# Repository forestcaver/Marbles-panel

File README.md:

# Marbles-Panel

1. My version of the marbles panel - bitmap, eagle files, gerbers
2. My spreadsheet to calibrate marbles and my version of settings.cc which includes my calibration data for my two modules.
3. Calibration document written by Bu Ma from some rough notes I sent - his are very clear instructions ! (Reproduced here by kind permission of Bu Ma !)
4. NOTE: When flashing the module make sure to erase flash first.
5. Added a mic803 supervisor, moved recom to the back of the pcb so it doesnt clash with the switch

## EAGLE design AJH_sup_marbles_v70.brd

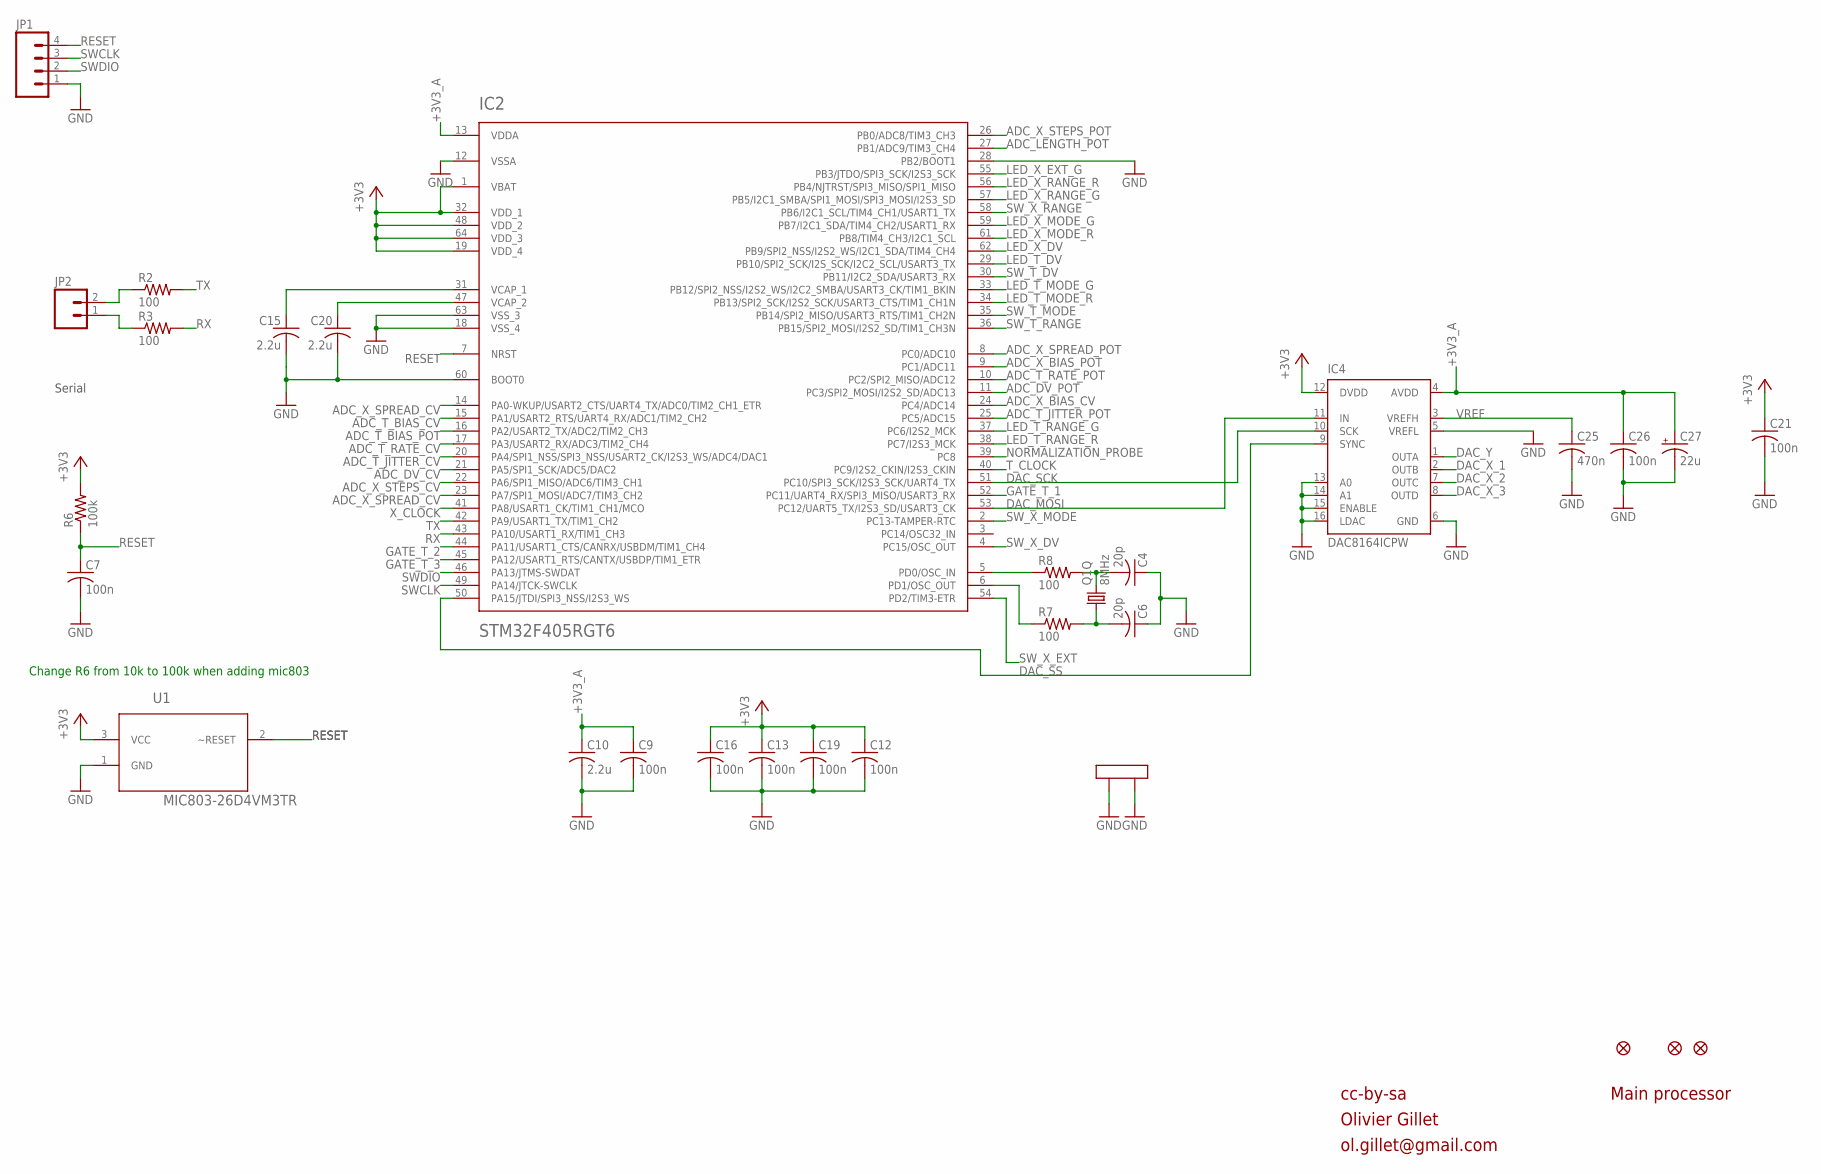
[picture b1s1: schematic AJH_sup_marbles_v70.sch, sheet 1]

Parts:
C4, C6: 20p; C0402
C7, C9, C12, C13, C16, C19, C21, C26: 100n; C0402
C10, C15, C20: 2.2u; C0805
C25: 470n; C0402
C27: 22u; PANASONIC_C
F1, F2, F3: FIDUCIAL1X2; FIDUCIAL-1X2
IC2: STM32F405RGT6; TQFP-10X10-64
IC4: DAC8164ICPW; SOP65P640X110-16N
JP1: M04PTH; 1X04
JP2: M02PTH; 1X02
Q1: 8MHz; CTS406
R2, R3, R7, R8: 100; R0402
R6: 100k; R0402
U1: MIC803-26D4VM3TR; SOT95P232X110-3N

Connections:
+3V3: C12.1, C13.1, C16.1, C19.1, C21.1, IC2.1 (VBAT), IC2.19 (VDD_4), IC2.32 (VDD_1), IC2.48 (VDD_2), IC2.64 (VDD_3), IC4.12 (DVDD), R6.2, U1.3 (VCC); also elsewhere on the board
+3V3_A: C9.1, C10.1, C26.1, C27.+, IC2.13 (VDDA), IC4.4 (AVDD); also elsewhere on the board
ADC_DV_CV: IC2.21 (PA5/SPI1_SCK/ADC5/DAC2); also elsewhere on the board
ADC_DV_POT: IC2.11 (PC3/SPI2_MOSI/I2S2_SD/ADC13); also elsewhere on the board
ADC_LENGTH_POT: IC2.27 (PB1/ADC9/TIM3_CH4); also elsewhere on the board
ADC_T_BIAS_CV: IC2.15 (PA1/USART2_RTS/UART4_RX/ADC1/TIM2_CH2); also elsewhere on the board
ADC_T_BIAS_POT: IC2.16 (PA2/USART2_TX/ADC2/TIM2_CH3); also elsewhere on the board
ADC_T_JITTER_CV: IC2.20 (PA4/SPI1_NSS/SPI3_NSS/USART2_CK/I2S3_WS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); also elsewhere on the board
ADC_T_JITTER_POT: IC2.25 (PC5/ADC15); also elsewhere on the board
ADC_T_RATE_CV: IC2.17 (PA3/USART2_RX/ADC3/TIM2_CH4); also elsewhere on the board
ADC_T_RATE_POT: IC2.10 (PC2/SPI2_MISO/ADC12); also elsewhere on the board
ADC_X_BIAS_CV: IC2.24 (PC4/ADC14); also elsewhere on the board
ADC_X_BIAS_POT: IC2.9 (PC1/ADC11); also elsewhere on the board
ADC_X_SPREAD_CV: IC2.14 (PA0-WKUP/USART2_CTS/UART4_TX/ADC0/TIM2_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), IC2.23 (PA7/SPI1_MOSI/ADC7/TIM3_CH2); also elsewhere on the board
ADC_X_SPREAD_POT: IC2.8 (PC0/ADC10); also elsewhere on the board
ADC_X_STEPS_CV: IC2.22 (PA6/SPI1_MISO/ADC6/TIM3_CH1); also elsewhere on the board
ADC_X_STEPS_POT: IC2.26 (PB0/ADC8/TIM3_CH3); also elsewhere on the board
DAC_MOSI: IC2.53 (PC12/UART5_TX/I2S3_SD/USART3_CK), IC4.11 (IN)
DAC_SCK: IC2.51 (PC10/SPI3_SCK/I2S3_SCK/UART4_TX), IC4.10 (SCK)
DAC_SS: IC2.50 (PA15/JTDI/SPI3_NSS/I2S3_WS), IC4.9 (SYNC)
DAC_X_1: IC4.2 (OUTB); also elsewhere on the board
DAC_X_2: IC4.7 (OUTC); also elsewhere on the board
DAC_X_3: IC4.8 (OUTD); also elsewhere on the board
DAC_Y: IC4.1 (OUTA); also elsewhere on the board
GATE_T_1: IC2.52 (PC11/UART4_RX/SPI3_MISO/USART3_RX); also elsewhere on the board
GATE_T_2: IC2.44 (PA11/USART1_CTS/CANRX/USBDM/TIM1_CH4); also elsewhere on the board
GATE_T_3: IC2.45 (PA12/USART1_RTS/CANTX/USBDP/TIM1_ETR); also elsewhere on the board
GND: C4.1, C6.1, C7.2, C9.2, C10.2, C12.2, C13.2, C15.2, C16.2, C19.2, C20.2, C21.2, C25.2, C26.2, C27.-, IC2.12 (VSSA), IC2.18 (VSS_4), IC2.28 (PB2/BOOT1), IC2.60 (BOOT0), IC2.63 (VSS_3), IC4.5 (VREFL), IC4.6 (GND), IC4.13 (A0), IC4.14 (A1), IC4.15 (ENABLE), IC4.16 (LDAC), JP1.1, Q1.2 (LID1), Q1.4 (LID2), U1.1 (GND); also elsewhere on the board
LED_T_DV: IC2.29 (PB10/SPI2_SCK/I2S_SCK/I2C2_SCL/USART3_TX); also elsewhere on the board
LED_T_MODE_G: IC2.33 (PB12/SPI2_NSS/I2S2_WS/I2C2_SMBA/USART3_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); also elsewhere on the board
LED_T_MODE_R: IC2.34 (PB13/SPI2_SCK/I2S2_SCK/USART3_CTS/TIM1_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); also elsewhere on the board
LED_T_RANGE_G: IC2.37 (PC6/I2S2_MCK); also elsewhere on the board
LED_T_RANGE_R: IC2.38 (PC7/I2S3_MCK); also elsewhere on the board
LED_X_DV: IC2.62 (PB9/SPI2_NSS/I2S2_WS/I2C1_SDA/TIM4_CH4); also elsewhere on the board
LED_X_EXT_G: IC2.55 (PB3/JTDO/SPI3_SCK/I2S3_SCK); also elsewhere on the board
LED_X_MODE_G: IC2.59 (PB7/I2C1_SDA/TIM4_CH2/USART1_RX); also elsewhere on the board
LED_X_MODE_R: IC2.61 (PB8/TIM4_CH3/I2C1_SCL); also elsewhere on the board
LED_X_RANGE_G: IC2.57 (PB5/I2C1_SMBA/SPI1_MOSI/SPI3_MOSI/I2S3_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); also elsewhere on the board
LED_X_RANGE_R: IC2.56 (PB4/NJTRST/SPI3_MISO/SPI1_MISO); also elsewhere on the board
unnamed: IC2.6 (PD1/OSC_OUT), R7.1
unnamed: IC2.5 (PD0/OSC_IN), R8.1
unnamed: C20.1, IC2.47 (VCAP_2)
unnamed: C15.1, IC2.31 (VCAP_1)
unnamed: JP2.2, R2.1
unnamed: JP2.1, R3.1
unnamed: C4.2, Q1.3 (2), R8.2
unnamed: C6.2, Q1.1, R7.2
NORMALIZATION_PROBE: IC2.39 (PC8); also elsewhere on the board
RESET: C7.1, IC2.7 (NRST), JP1.4, R6.1, U1.2 (~RESET)
RX: IC2.43 (PA10/USART1_RX/TIM1_CH3), R3.2
SWCLK: IC2.49 (PA14/JTCK-SWCLK), JP1.3
SWDIO: IC2.46 (PA13/JTMS-SWDAT), JP1.2
SW_T_DV: IC2.30 (PB11/I2C2_SDA/USART3_RX); also elsewhere on the board
SW_T_MODE: IC2.35 (PB14/SPI2_MISO/USART3_RTS/TIM1_CH2N); also elsewhere on the board
SW_T_RANGE: IC2.36 (PB15/SPI2_MOSI/I2S2_SD/TIM1_CH3N); also elsewhere on the board
SW_X_DV: IC2.4 (PC15/OSC_OUT); also elsewhere on the board
SW_X_EXT: IC2.54 (PD2/TIM3-ETR); also elsewhere on the board
SW_X_MODE: IC2.2 (PC13-TAMPER-RTC); also elsewhere on the board
SW_X_RANGE: IC2.58 (PB6/I2C1_SCL/TIM4_CH1/USART1_TX); also elsewhere on the board
TX: IC2.42 (PA9/USART1_TX/TIM1_CH2), R2.2
T_CLOCK: IC2.40 (PC9/I2S2_CKIN/I2S3_CKIN); also elsewhere on the board
VREF: C25.1, IC4.3 (VREFH); also elsewhere on the board
X_CLOCK: IC2.41 (PA8/USART1_CK/TIM1_CH1/MCO); also elsewhere on the board

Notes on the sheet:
cc-by-sa
Olivier Gillet
ol.gillet@gmail.com
Main processor
Serial
Change R6 from 10k to 100k when adding mic803

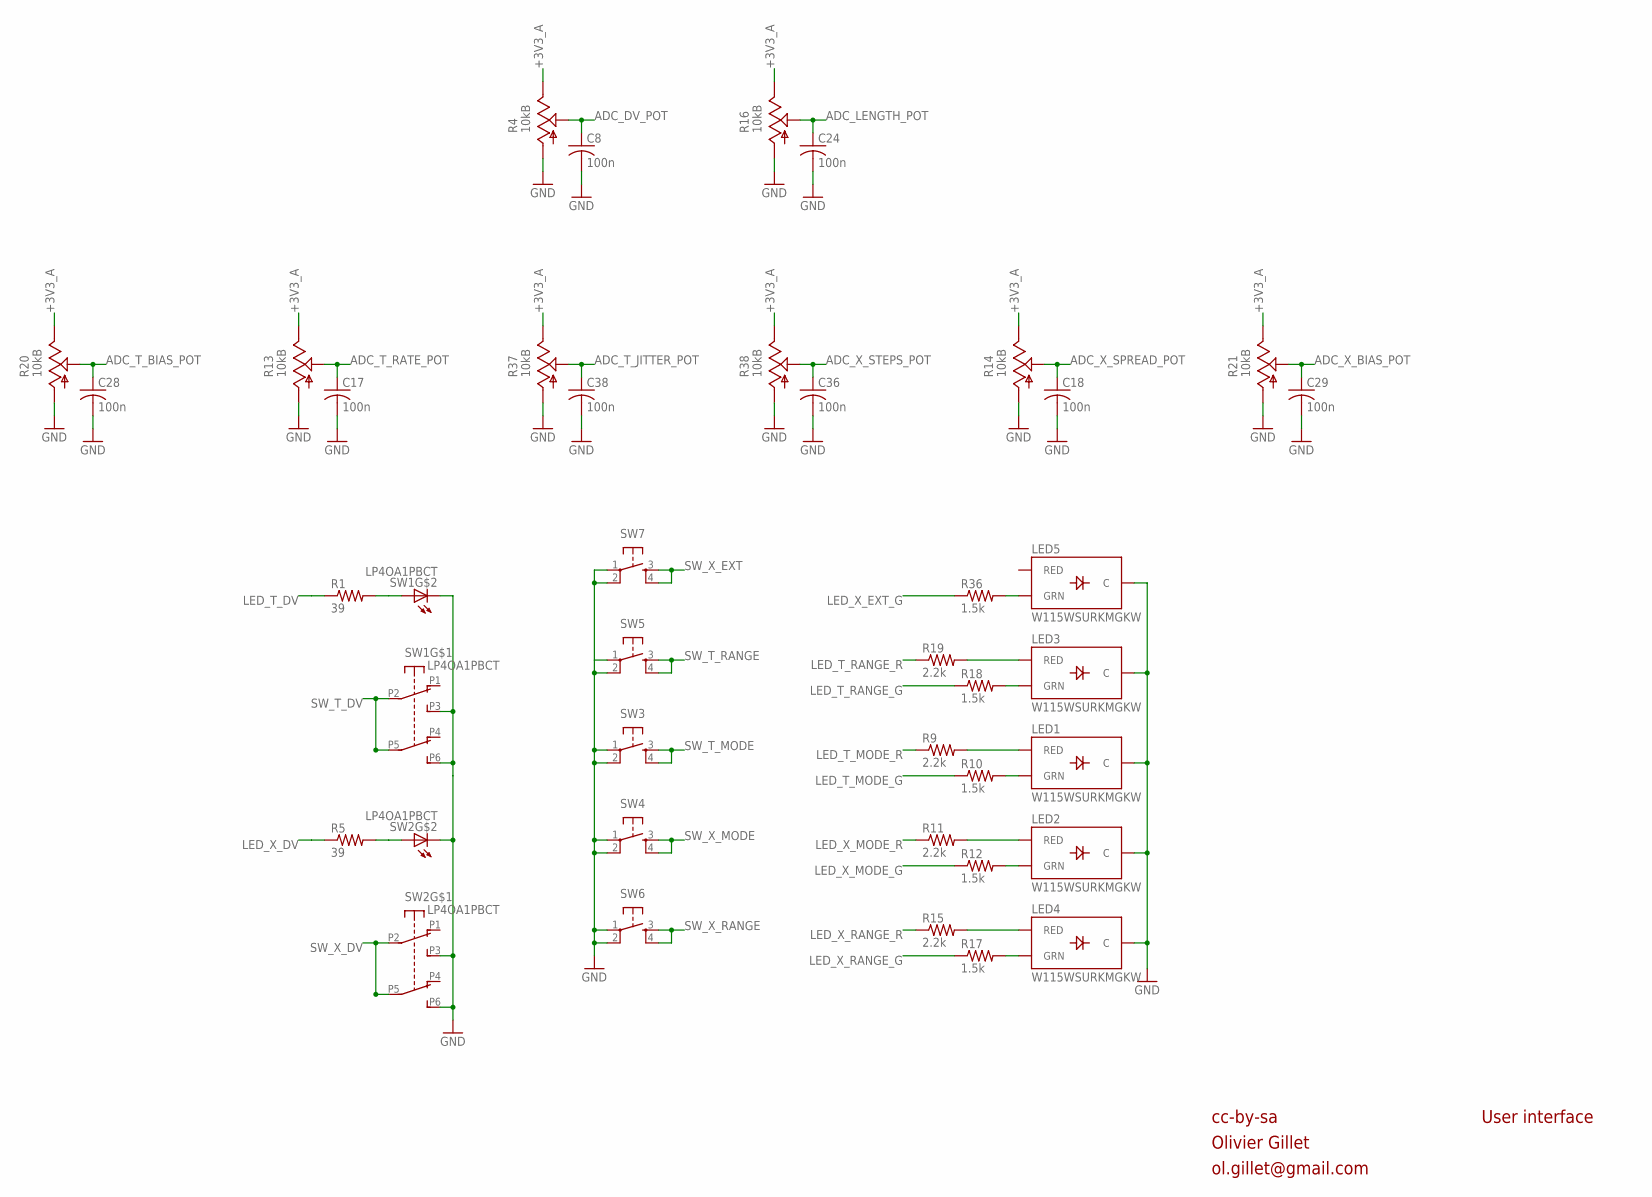
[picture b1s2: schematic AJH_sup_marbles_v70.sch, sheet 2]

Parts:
C8, C17, C18, C24, C28, C29, C36, C38: 100n; C0402
LED1, LED2, LED3, LED4, LED5: W115WSURKMGKW; LED-BICOLOR-THROUGHHOLE-2.54
R1, R5: 39; R0402
R4, R13, R14, R16, R20, R21, R37, R38: 10kB; ALPS_POT_VERTICAL_PS
R9, R11, R15, R19: 2.2k; R0402
R10, R12, R17, R18, R36: 1.5k; R0402
SW1, SW2: LP4OA1PBCT
SW3, SW4, SW5, SW6, SW7: TAC_SWITCHPTH; TACTILE-PTH

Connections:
+3V3_A: R4.P$1 (E), R13.P$1 (E), R14.P$1 (E), R16.P$1 (E), R20.P$1 (E), R21.P$1 (E), R37.P$1 (E), R38.P$1 (E); also elsewhere on the board
ADC_DV_POT: C8.1, R4.P$2 (S); also elsewhere on the board
ADC_LENGTH_POT: C24.1, R16.P$2 (S); also elsewhere on the board
ADC_T_BIAS_POT: C28.1, R20.P$2 (S); also elsewhere on the board
ADC_T_JITTER_POT: C38.1, R37.P$2 (S); also elsewhere on the board
ADC_T_RATE_POT: C17.1, R13.P$2 (S); also elsewhere on the board
ADC_X_BIAS_POT: C29.1, R21.P$2 (S); also elsewhere on the board
ADC_X_SPREAD_POT: C18.1, R14.P$2 (S); also elsewhere on the board
ADC_X_STEPS_POT: C36.1, R38.P$2 (S); also elsewhere on the board
GND: C8.2, C17.2, C18.2, C24.2, C28.2, C29.2, C36.2, C38.2, LED1.2 (C), LED2.2 (C), LED3.2 (C), LED4.2 (C), LED5.2 (C), R4.P$3 (A), R13.P$3 (A), R14.P$3 (A), R16.P$3 (A), R20.P$3 (A), R21.P$3 (A), R37.P$3 (A), R38.P$3 (A), SW1.L2, SW1.P3 (A3), SW1.P6 (B3), SW2.L2, SW2.P3 (A3), SW2.P6 (B3), SW3.1, SW3.2, SW4.1, SW4.2, SW5.1, SW5.2, SW6.1, SW6.2, SW7.1, SW7.2; also elsewhere on the board
LED_T_DV: R1.1; also elsewhere on the board
LED_T_MODE_G: R10.1; also elsewhere on the board
LED_T_MODE_R: R9.1; also elsewhere on the board
LED_T_RANGE_G: R18.1; also elsewhere on the board
LED_T_RANGE_R: R19.1; also elsewhere on the board
LED_X_DV: R5.1; also elsewhere on the board
LED_X_EXT_G: R36.1; also elsewhere on the board
LED_X_MODE_G: R12.1; also elsewhere on the board
LED_X_MODE_R: R11.1; also elsewhere on the board
LED_X_RANGE_G: R17.1; also elsewhere on the board
LED_X_RANGE_R: R15.1; also elsewhere on the board
unnamed: R1.2, SW1.L1
unnamed: R5.2, SW2.L1
unnamed: LED3.3 (RED), R19.2
unnamed: LED3.1 (GRN), R18.2
unnamed: LED1.3 (RED), R9.2
unnamed: LED2.3 (RED), R11.2
unnamed: LED2.1 (GRN), R12.2
unnamed: LED4.3 (RED), R15.2
unnamed: LED1.1 (GRN), R10.2
unnamed: LED4.1 (GRN), R17.2
unnamed: LED5.1 (GRN), R36.2
SW_T_DV: SW1.P2 (A2), SW1.P5 (B2); also elsewhere on the board
SW_T_MODE: SW3.3, SW3.4; also elsewhere on the board
SW_T_RANGE: SW5.3, SW5.4; also elsewhere on the board
SW_X_DV: SW2.P2 (A2), SW2.P5 (B2); also elsewhere on the board
SW_X_EXT: SW7.3, SW7.4; also elsewhere on the board
SW_X_MODE: SW4.3, SW4.4; also elsewhere on the board
SW_X_RANGE: SW6.3, SW6.4; also elsewhere on the board

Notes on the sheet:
cc-by-sa
Olivier Gillet
ol.gillet@gmail.com
User interface

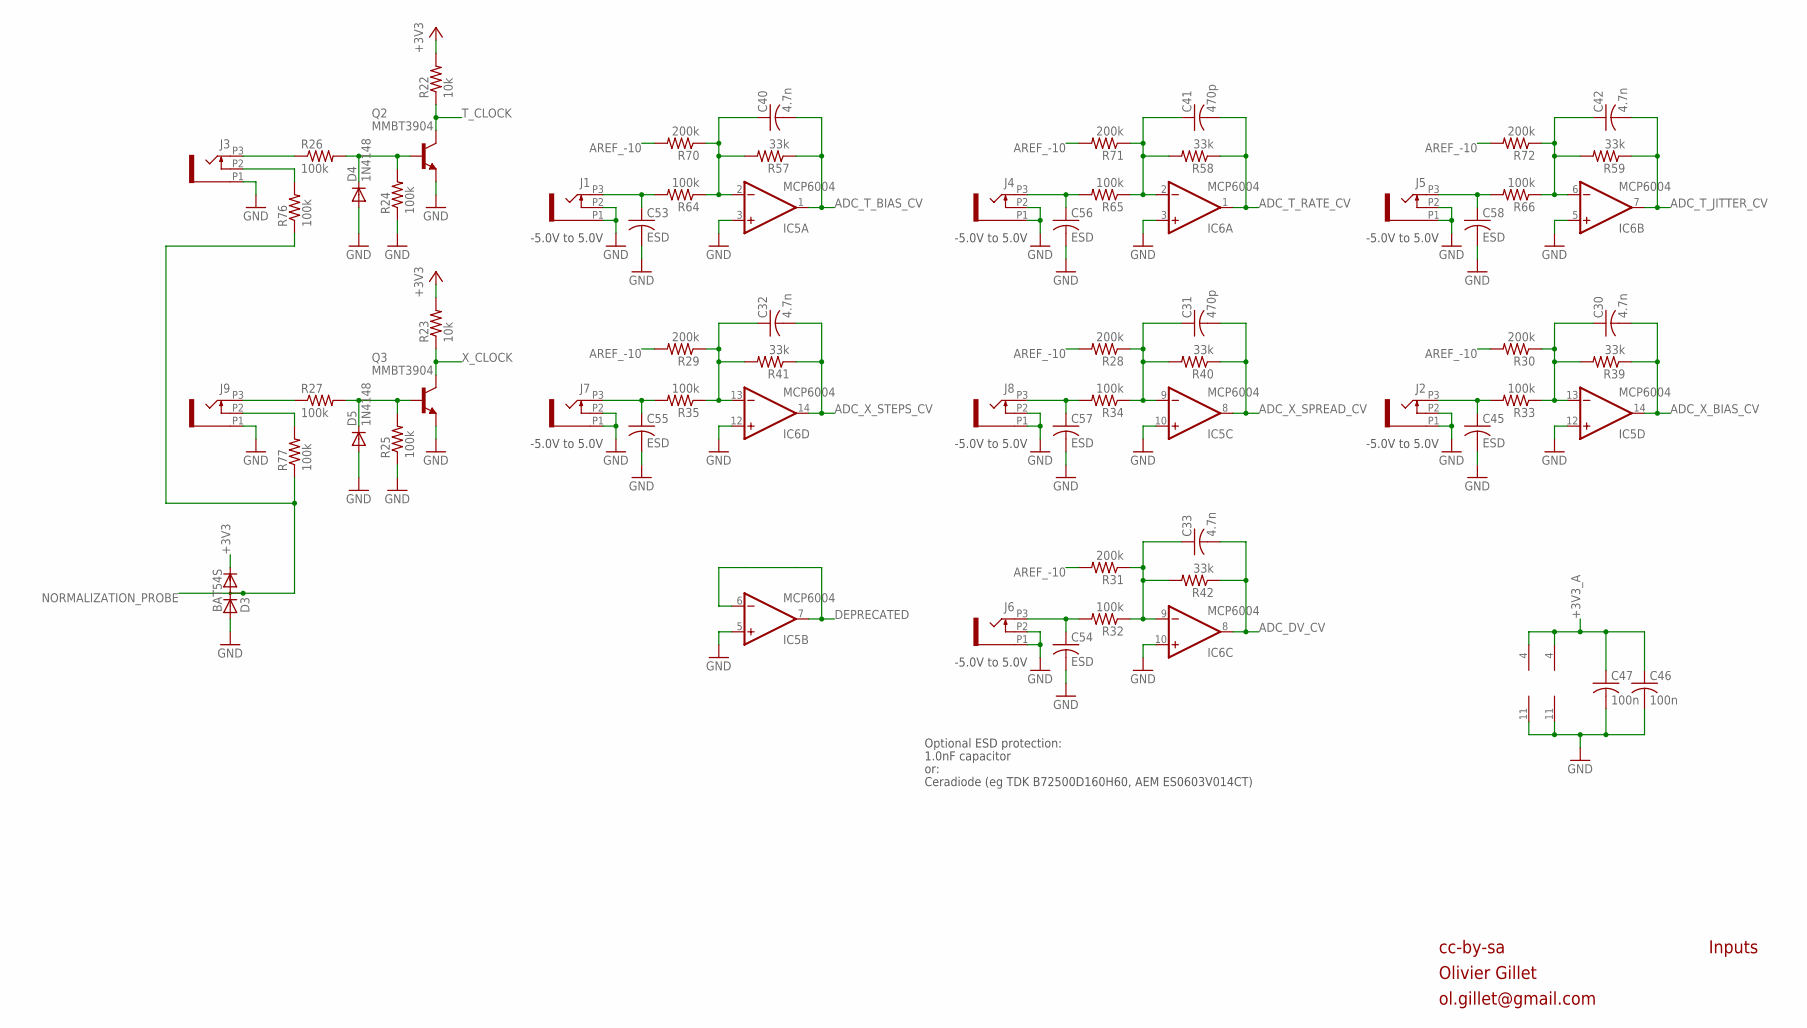
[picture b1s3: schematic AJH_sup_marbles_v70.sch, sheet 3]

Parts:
C30, C32, C33, C40, C42: 4.7n; C0402
C31, C41: 470p; C0402
C45, C53, C54, C55, C56, C57, C58: ESD; C0603
C46, C47: 100n; C0402
D3: BAT54S; SOT23
D4, D5: 1N4148; SOD523
IC5, IC6: MCP6004; TSSOP14_065
J1, J2, J3, J4, J5, J6, J7, J8, J9: PJ301_THONKICONN6; WQP_PJ_301M6
Q2, Q3: MMBT3904; SOT23-BEC
R22, R23: 10k; R0402
R24, R25, R26, R27, R32, R33, R34, R35, R64, R65, R66, R76, R77: 100k; R0402
R28, R29, R30, R31, R70, R71, R72: 200k; R0402
R39, R40, R41, R42, R57, R58, R59: 33k; R0402

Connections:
+3V3: D3.2 (C), R22.2, R23.2; also elsewhere on the board
+3V3_A: C46.1, C47.1, IC5.4 (V+), IC6.4 (V+); also elsewhere on the board
ADC_DV_CV: C33.2, IC6.8 (OUT), R42.1; also elsewhere on the board
ADC_T_BIAS_CV: C40.2, IC5.1 (OUT), R57.1; also elsewhere on the board
ADC_T_JITTER_CV: C42.2, IC6.7 (OUT), R59.1; also elsewhere on the board
ADC_T_RATE_CV: C41.2, IC6.1 (OUT), R58.1; also elsewhere on the board
ADC_X_BIAS_CV: C30.2, IC5.14 (OUT), R39.1; also elsewhere on the board
ADC_X_SPREAD_CV: C31.2, IC5.8 (OUT), R40.1; also elsewhere on the board
ADC_X_STEPS_CV: C32.2, IC6.14 (OUT), R41.1; also elsewhere on the board
AREF_-10: R28.2, R29.2, R30.2, R31.2, R70.2, R71.2, R72.2; also elsewhere on the board
DEPRECATED: IC5.6 (-IN), IC5.7 (OUT)
GND: C45.2, C46.2, C47.2, C53.2, C54.2, C55.2, C56.2, C57.2, C58.2, D3.1 (A), D4.A, D5.A, IC5.3 (+IN), IC5.5 (+IN), IC5.10 (+IN), IC5.11 (V-), IC5.12 (+IN), IC6.3 (+IN), IC6.5 (+IN), IC6.10 (+IN), IC6.11 (V-), IC6.12 (+IN), J1.P1 (1), J1.P2 (2), J2.P1 (1), J2.P2 (2), J3.P1 (1), J4.P1 (1), J4.P2 (2), J5.P1 (1), J5.P2 (2), J6.P1 (1), J6.P2 (2), J7.P1 (1), J7.P2 (2), J8.P1 (1), J8.P2 (2), J9.P1 (1), Q2.E, Q3.E, R24.1, R25.1; also elsewhere on the board
MORPH_IN: C53.1, J1.P3 (3), R64.2
MORPH_IN1: C55.1, J7.P3 (3), R35.2
MORPH_IN3: C56.1, J4.P3 (3), R65.2
MORPH_IN4: C57.1, J8.P3 (3), R34.2
MORPH_IN5: C54.1, J6.P3 (3), R32.2
MORPH_IN6: C58.1, J5.P3 (3), R66.2
MORPH_IN7: C45.1, J2.P3 (3), R33.2
unnamed: C41.1, IC6.2 (-IN), R58.2, R65.1, R71.1
unnamed: C40.1, IC5.2 (-IN), R57.2, R64.1, R70.1
unnamed: C42.1, IC6.6 (-IN), R59.2, R66.1, R72.1
unnamed: C31.1, IC5.9 (-IN), R28.1, R34.1, R40.2
unnamed: C30.1, IC5.13 (-IN), R30.1, R33.1, R39.2
unnamed: C32.1, IC6.13 (-IN), R29.1, R35.1, R41.2
unnamed: C33.1, IC6.9 (-IN), R31.1, R32.1, R42.2
unnamed: J9.P3 (3), R27.1
unnamed: J9.P2 (2), R77.2
unnamed: J3.P2 (2), R76.2
unnamed: D4.C, Q2.B, R24.2, R26.2
unnamed: D5.C, Q3.B, R25.2, R27.2
unnamed: J3.P3 (3), R26.1
NORMALIZATION_PROBE: D3.3 (AC), R76.1, R77.1; also elsewhere on the board
T_CLOCK: Q2.C, R22.1; also elsewhere on the board
X_CLOCK: Q3.C, R23.1; also elsewhere on the board

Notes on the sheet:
cc-by-sa
Olivier Gillet
ol.gillet@gmail.com
Inputs
-5.0V to 5.0V
Optional ESD protection:
1.0nF capacitor
or:
Ceradiode (eg TDK B72500D160H60, AEM ES0603V014CT)

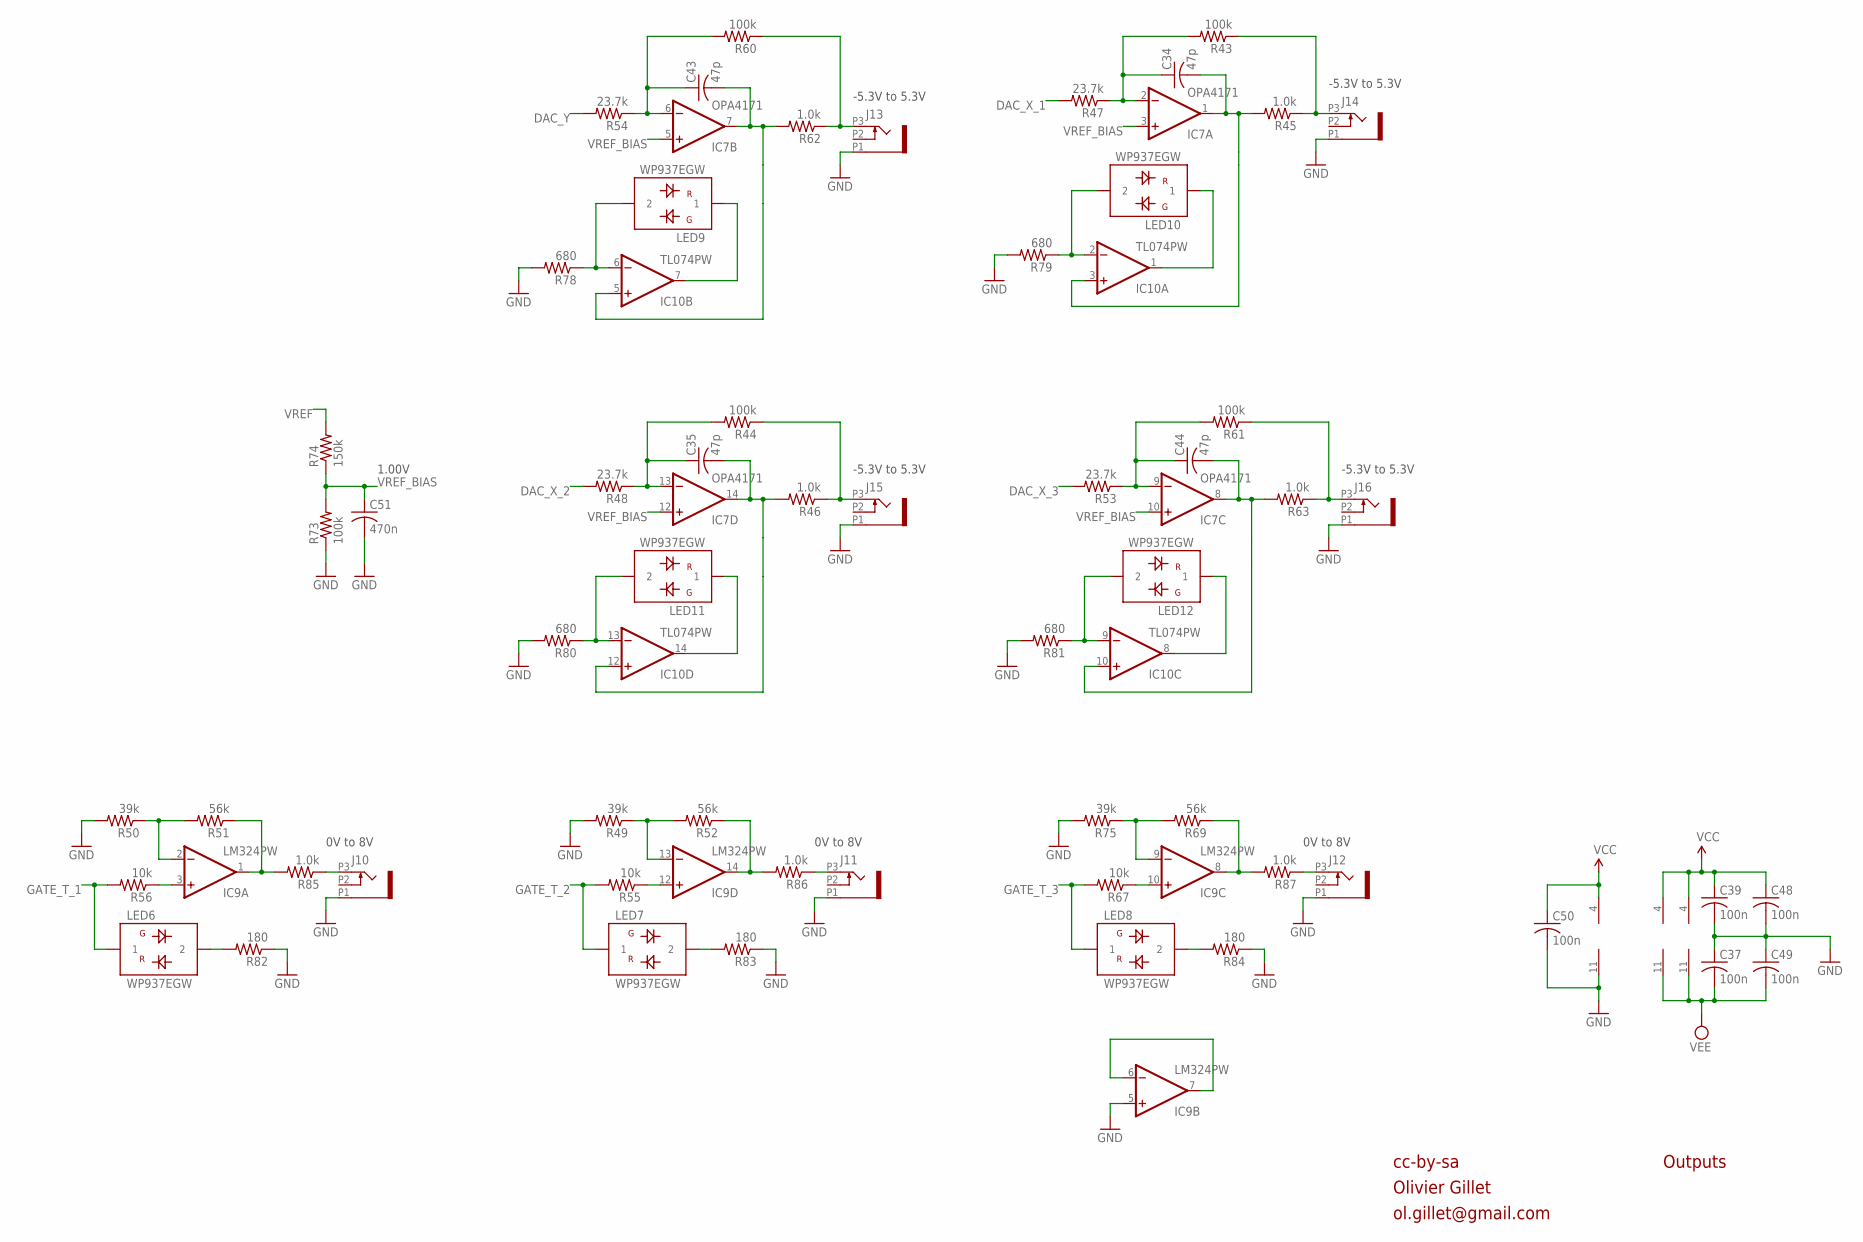
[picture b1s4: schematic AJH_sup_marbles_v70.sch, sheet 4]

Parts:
C34, C35, C43, C44: 47p; C0402
C37, C39, C48, C49, C50: 100n; C0402
C51: 470n; C0402
IC7: OPA4171; TSSOP14_065
IC9: LM324PW; TSSOP14_065
IC10: TL074PW; TSSOP14_065
J10, J11, J12, J13, J14, J15, J16: PJ301_THONKICONN6; WQP_PJ_301M6
LED6, LED7, LED8, LED9, LED10, LED11, LED12: WP937EGW; LED3MM
R43, R44, R60, R61, R73: 100k; R0402
R45, R46, R62, R63, R85, R86, R87: 1.0k; R0603
R47, R48, R53, R54: 23.7k; R0402
R49, R50, R75: 39k; R0402
R51, R52, R69: 56k; R0402
R55, R56, R67: 10k; R0402
R74: 150k; R0402
R78, R79, R80, R81: 680; R0402
R82, R83, R84: 180; R0402

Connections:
DAC_X_1: R47.2; also elsewhere on the board
DAC_X_2: R48.2; also elsewhere on the board
DAC_X_3: R53.2; also elsewhere on the board
DAC_Y: R54.2; also elsewhere on the board
GATE_T_1: LED6.1, R56.2; also elsewhere on the board
GATE_T_2: LED7.1, R55.2; also elsewhere on the board
GATE_T_3: LED8.1, R67.2; also elsewhere on the board
GND: C37.1, C39.2, C48.2, C49.1, C50.2, C51.2, IC9.5 (+IN), IC9.11 (V-), J10.P1 (1), J11.P1 (1), J12.P1 (1), J13.P1 (1), J14.P1 (1), J15.P1 (1), J16.P1 (1), R49.2, R50.2, R73.1, R75.2, R78.2, R79.2, R80.2, R81.2, R82.1, R83.1, R84.1; also elsewhere on the board
unnamed: IC9.12 (+IN), R55.1
unnamed: IC9.1 (OUT), R51.1, R85.2
unnamed: J10.P3 (3), R85.1
unnamed: IC9.2 (-IN), R50.1, R51.2
unnamed: LED6.2, R82.2
unnamed: IC9.3 (+IN), R56.1
unnamed: IC9.6 (-IN), IC9.7 (OUT)
unnamed: IC9.14 (OUT), R52.1, R86.2
unnamed: IC9.13 (-IN), R49.1, R52.2
unnamed: IC9.10 (+IN), R67.1
unnamed: IC9.8 (OUT), R69.1, R87.2
unnamed: J11.P3 (3), R86.1
unnamed: J12.P3 (3), R87.1
unnamed: IC9.9 (-IN), R69.2, R75.1
unnamed: LED7.2, R83.2
unnamed: C43.2, IC7.7 (OUT), IC10.5 (+IN), R62.2
unnamed: LED8.2, R84.2
unnamed: J15.P3 (3), R44.1, R46.1
unnamed: J13.P3 (3), R60.1, R62.1
unnamed: C35.1, IC7.13 (-IN), R44.2, R48.1
unnamed: J16.P3 (3), R61.1, R63.1
unnamed: C44.1, IC7.9 (-IN), R53.1, R61.2
unnamed: C34.1, IC7.2 (-IN), R43.2, R47.1
unnamed: C43.1, IC7.6 (-IN), R54.1, R60.2
unnamed: J14.P3 (3), R43.1, R45.1
unnamed: IC10.6 (-IN), LED9.2, R78.1
unnamed: IC10.7 (OUT), LED9.1
unnamed: C34.2, IC7.1 (OUT), IC10.3 (+IN), R45.2
unnamed: IC10.2 (-IN), LED10.2, R79.1
unnamed: IC10.1 (OUT), LED10.1
unnamed: C35.2, IC7.14 (OUT), IC10.12 (+IN), R46.2
unnamed: IC10.13 (-IN), LED11.2, R80.1
unnamed: IC10.14 (OUT), LED11.1
unnamed: C44.2, IC7.8 (OUT), IC10.10 (+IN), R63.2
unnamed: IC10.9 (-IN), LED12.2, R81.1
unnamed: IC10.8 (OUT), LED12.1
VCC: C39.1, C48.1, C50.1, IC7.4 (V+), IC9.4 (V+), IC10.4 (V+); also elsewhere on the board
VEE: C37.2, C49.2, IC7.11 (V-), IC10.11 (V-); also elsewhere on the board
VREF: R74.2; also elsewhere on the board
VREF_BIAS: C51.1, IC7.3 (+IN), IC7.5 (+IN), IC7.10 (+IN), IC7.12 (+IN), R73.2, R74.1

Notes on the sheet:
-5.3V to 5.3V
0V to 8V
cc-by-sa
Olivier Gillet
ol.gillet@gmail.com
Outputs
1.00V

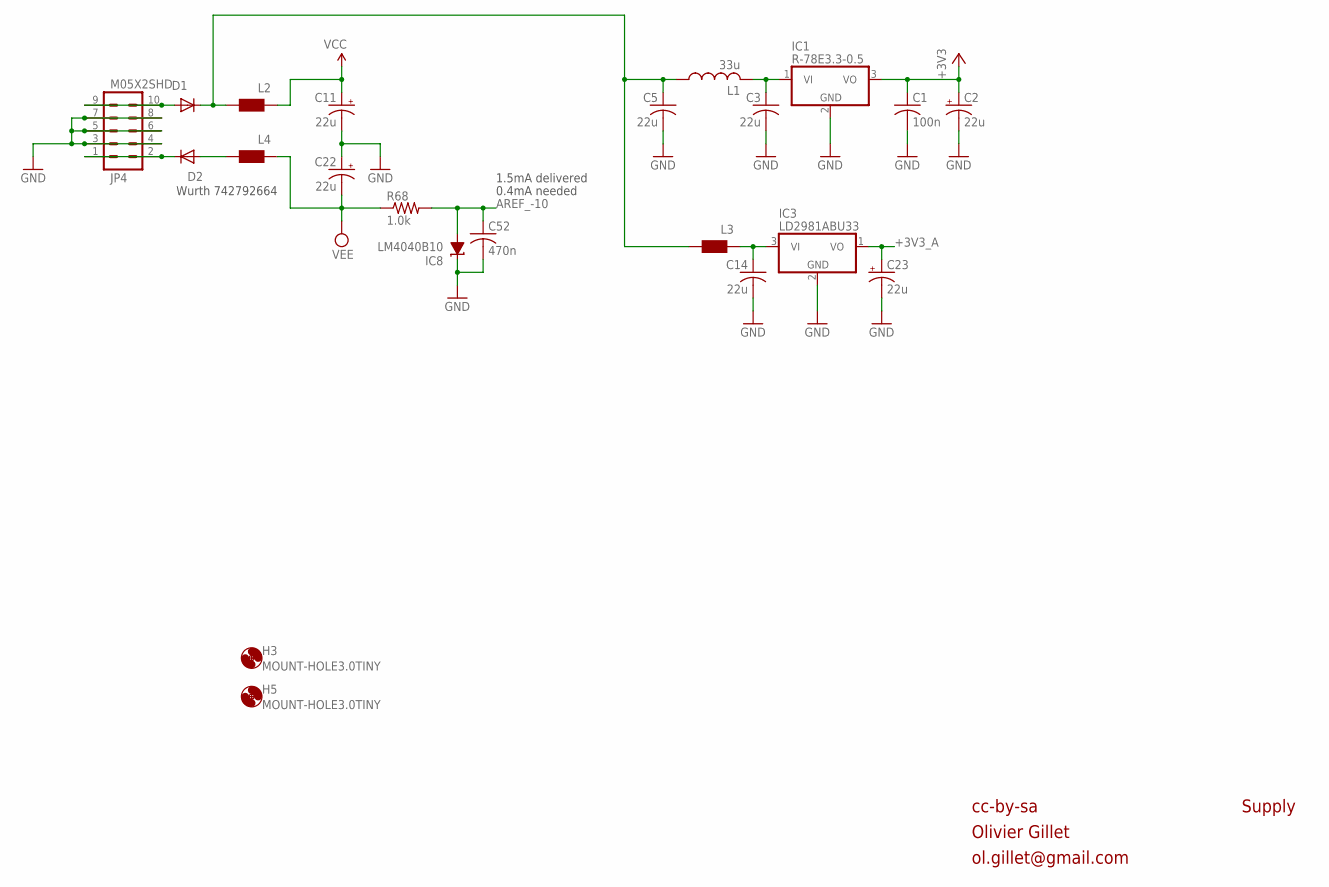
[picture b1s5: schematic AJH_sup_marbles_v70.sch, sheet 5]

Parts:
C1: 100n; C0402
C2, C11, C22, C23: 22u; PANASONIC_C
C3, C5, C14: 22u; C1206
C52: 470n; C0402
D1, D2: 1N5819HW; SOD123
H3, H5: MOUNT-HOLE3.0TINY; 3,0TINY
IC1: R-78E3.3-0.5; WE78
IC3: LD2981ABU33; SOT89
IC8: LM4040B10; DBZ_R-PDSO-G3
JP4: M05X2SHD; 2X5-SHROUDED
L1: 33u; L2012C
L2, L3, L4: WE-CBF_0603; 0603
R68: 1.0k; R0402

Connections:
+3V3: C1.1, C2.+, IC1.3 (VO); also elsewhere on the board
+3V3_A: C23.+, IC3.1 (VO); also elsewhere on the board
AREF_-10: C52.1, IC8.2 (A), R68.2; also elsewhere on the board
GND: C1.2, C2.-, C3.2, C5.2, C11.-, C14.2, C22.+, C23.-, C52.2, IC1.2 (GND), IC3.2 (GND), IC8.1 (C), JP4.3, JP4.4, JP4.5, JP4.6, JP4.7, JP4.8; also elsewhere on the board
unnamed: C14.1, IC3.3 (VI), L3.1
unnamed: C5.1, D1.C, L1.1, L2.2, L3.2
unnamed: D2.A, L4.2
unnamed: C3.1, IC1.1 (VI), L1.2
unnamed: D1.A, JP4.9, JP4.10
unnamed: D2.C, JP4.1, JP4.2
VCC: C11.+, L2.1; also elsewhere on the board
VEE: C22.-, L4.1, R68.1; also elsewhere on the board

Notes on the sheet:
0.4mA needed
cc-by-sa
Olivier Gillet
ol.gillet@gmail.com
Supply
Wurth 742792664
1.5mA delivered

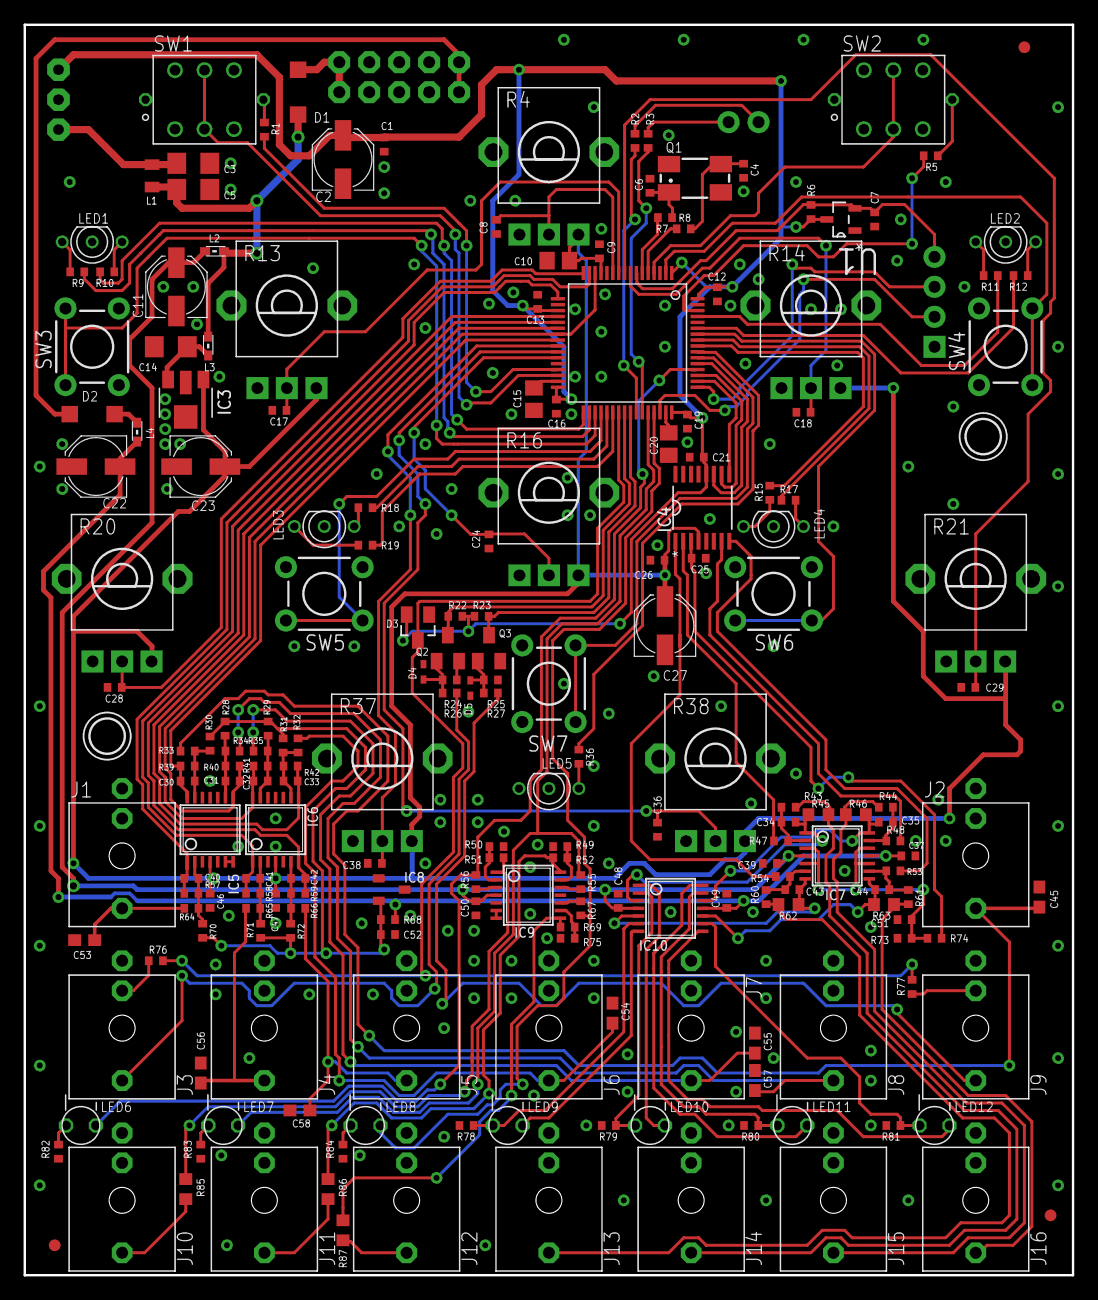
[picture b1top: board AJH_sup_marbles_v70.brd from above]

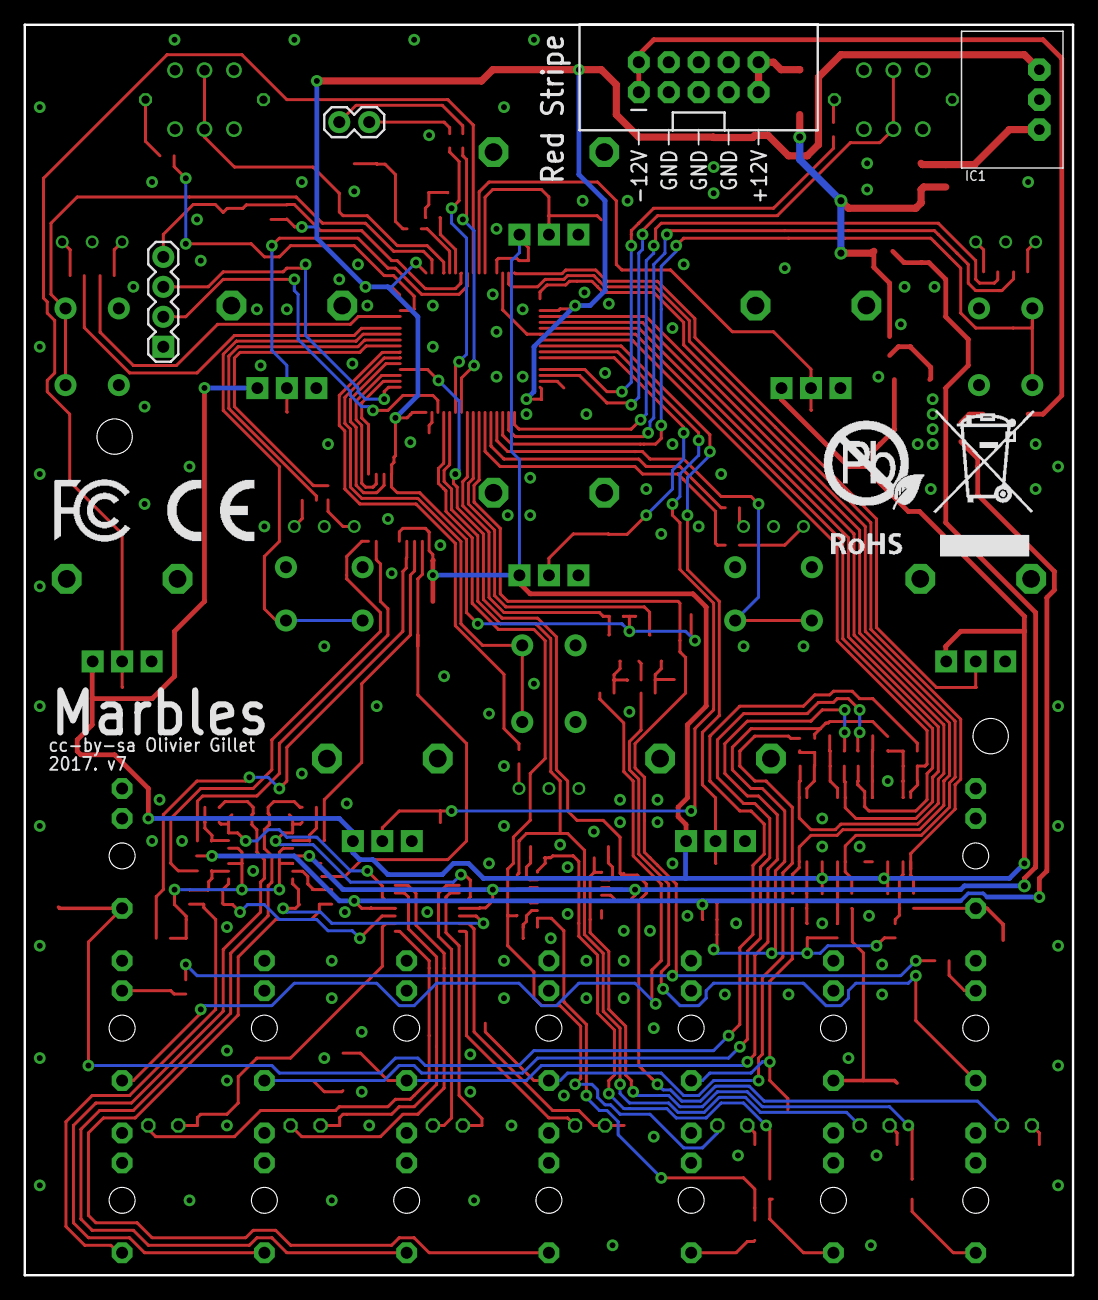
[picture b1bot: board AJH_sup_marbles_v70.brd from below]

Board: 2 copper layers, 88.9 x 106.0 mm, 214 parts (7 on the bottom side), 141 nets.

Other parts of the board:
U$2: ROHS_BIG
U$4: CE_MEDIUM
U$5: FCC_MEDIUM

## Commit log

2018-10-25 Add files via upload
    Marbles calibration file and spreadsheet for my particular modules
2019-01-17 Module 3 added
2021-03-02 Add supervisor, move recom
